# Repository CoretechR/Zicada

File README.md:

# Zicada - DIY Zigbee Multisensor

## Overview

Zicada is a DIY Zigbee sensor based on Nordic’s nRF52840 SoC. It combines a temperature and humidity sensor with a hall effect switch, making it suitable for both climate and door/window monitoring. Zicada is optimized for ultra-low power consumption, running at just 6µW in standby. This allows it to operate on a rechargeable AAA battery for 2 years or longer. It is fully compatible with Home Assistant (ZHA) and Zigbee2MQTT.

<div align="center">
  
</div>

### Features
* Temperature, humidity and contact sensing
* Zigbee 3.0 end device
* Compatible with Home Assistant (ZHA) and Zigbee2MQTT
* Ultra-low power consumption (6µW in Standby)
* 2+ years of battery life
* Supports AAA cells from 0.9V to 1.5V
* Small sized (62 x 15 mm) and fully 3D-printed case

### Setup Instructions

Follow these instructions to download and install the nRF Connect SDK version 2.6.0:
https://docs.nordicsemi.com/bundle/ncs-2.6.3/page/nrf/installation/install_ncs.html
Copy Zicada firmware folder into the directory ncs/projects.

When using the contact sensor with Zigbee2MQTT, copy the file "zicada_converter.js" to the directory data/external_converters/ of you Z2M install.

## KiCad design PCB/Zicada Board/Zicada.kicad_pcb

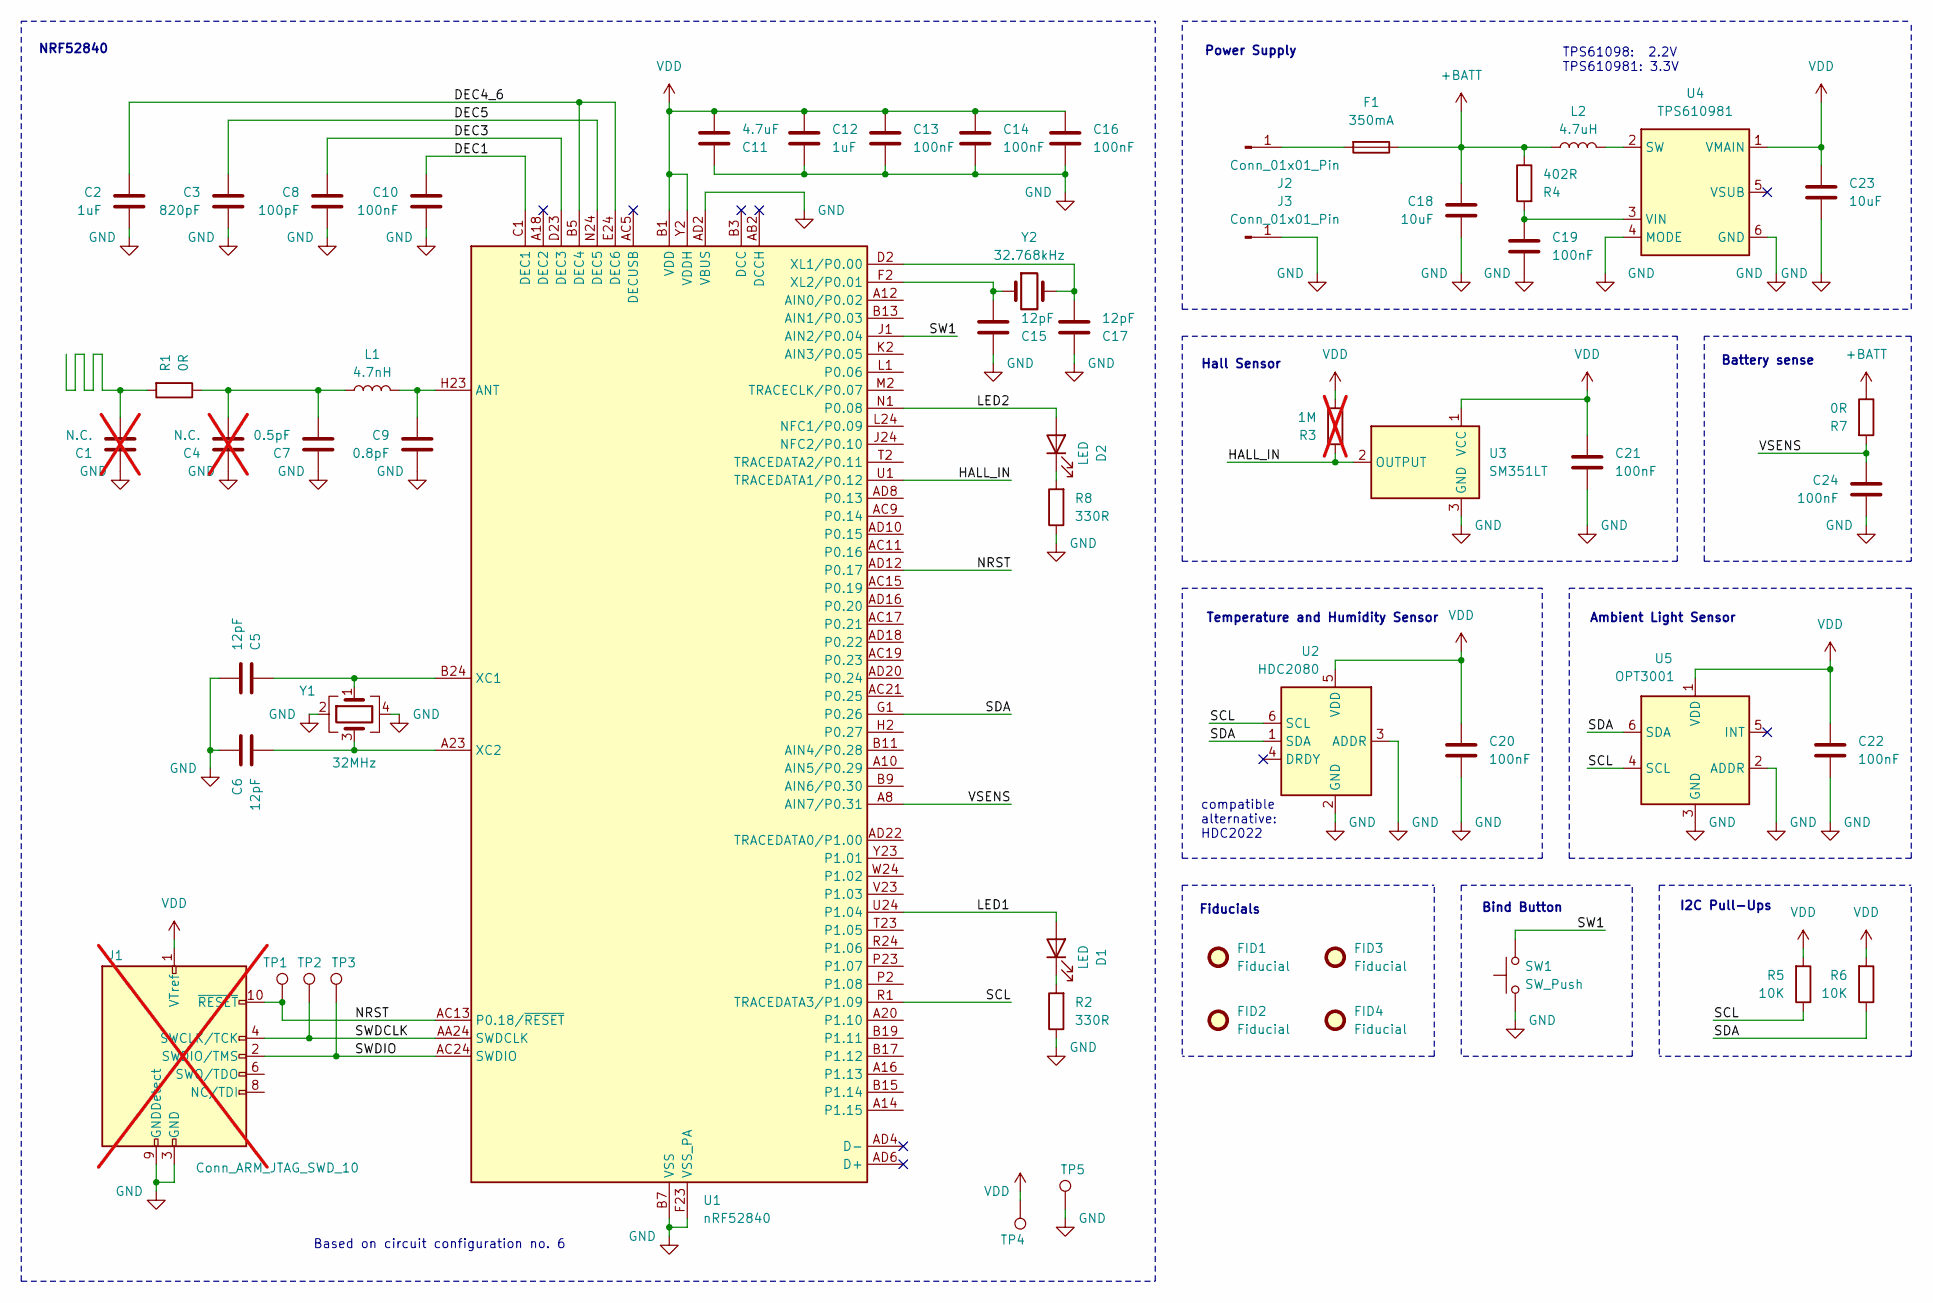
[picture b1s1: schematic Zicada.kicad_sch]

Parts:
C1, C4: N.C.; C_0603_1608Metric; not fitted
C2, C12: 1uF; C_0603_1608Metric; LCSC C15849
C3: 820pF; C_0603_1608Metric; LCSC C107057
C5, C6, C15, C17: 12pF; C_0603_1608Metric; LCSC C107034
C7: 0.5pF; C_0603_1608Metric; LCSC C5137584
C8: 100pF; C_0603_1608Metric; LCSC C14858
C9: 0.8pF; C_0603_1608Metric; LCSC C519369
C10, C13, C14, C16, C19, C20, C21, C22, C24: 100nF; C_0603_1608Metric; LCSC C1591
C11: 4.7uF; C_0603_1608Metric; LCSC C1705
C18, C23: 10uF; C_0603_1608Metric; LCSC C19702
D1, D2: LED; LED_0603_1608Metric; LCSC C5875723
F1: 350mA; Fuse_0805_2012Metric; LCSC C207021
FID1, FID2, FID3, FID4: Fiducial; Fiducial_1mm_Mask2mm
J1: Conn_ARM_JTAG_SWD_10; PinHeader_2x05_P1.27mm_Vertical_SMD; not fitted
J2, J3: Conn_01x01_Pin; MYOUNG MY-AAA-07; LCSC C6937109
L1: 4.7nH; L_0603_1608Metric; LCSC C1030
L2: 4.7uH; L_1008_2520Metric; LCSC C280597
R1, R7: 0R; R_0603_1608Metric; LCSC C116699
R2, R8: 330R; R_0603_1608Metric; LCSC C105881
R3: 1M; R_0603_1608Metric; LCSC C105578; not fitted
R4: 402R; R_0603_1608Metric; LCSC C227889
R5, R6: 10K; R_0603_1608Metric; LCSC C98220
SW1: SW_Push; SW_SPST_B3U-1000P-B; LCSC C231329
TP1, TP2, TP3, TP4, TP5: TestPoint; TestPoint_Pad_D1.5mm
U1: nRF52840; Nordic_AQFN-73-1EP_7x7mm_P0.5mm; LCSC C190794
U2: HDC2080; Texas_PWSON-N6; LCSC C918141
U3: SM351LT; SOT-23; LCSC C80830
U4: TPS610981; WSON-6_1.5x1.5mm_P0.5mm; LCSC C470966
U5: OPT3001; USON-6-1EP_2x2mm_P0.65mm_EP0.65x1.35mm; LCSC C90462
Y1: 32MHz; Crystal_SMD_Abracon_ABM8G-4Pin_3.2x2.5mm; LCSC C5552502
Y2: 32.768kHz; Crystal_SMD_MicroCrystal_CC7V-T1A-2Pin_3.2x1.5mm; LCSC C32346

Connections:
+BATT: C18.1, F1.1, L2.1, R4.1, R7.1
/DEC1: C10.1, U1.C1 (DEC1)
/DEC3: C8.1, U1.D23 (DEC3)
/DEC4_6: C2.1, U1.B5 (DEC4), U1.E24 (DEC6)
/DEC5: C3.1, U1.N24 (DEC5)
/HALL_IN: R3.2, U1.U1 (TRACEDATA1/P0.12), U3.2 (OUTPUT)
/LED1: D1.2 (A), U1.U24 (P1.04)
/LED2: D2.2 (A), U1.N1 (P0.08)
/NRST: J1.10 (~RESET), TP1.1, U1.AC13 (P0.18/~RESET), U1.AD12 (P0.17)
/SCL: R5.1, U1.R1 (TRACEDATA3/P1.09), U2.6 (SCL), U5.4 (SCL)
/SDA: R6.1, U1.G1 (P0.26), U2.1 (SDA), U5.6 (SDA)
/SW1: SW1.2, U1.J1 (AIN2/P0.04)
/SWDCLK: J1.4 (SWCLK/TCK), TP2.1, U1.AA24 (SWDCLK)
/SWDIO: J1.2 (SWDIO/TMS), TP3.1, U1.AC24 (SWDIO)
/VSENS: C24.1, R7.2, U1.A8 (AIN7/P0.31)
GND: C1.1, C2.2, C3.2, C4.1, C5.2, C6.1, C7.1, C8.2, C9.2, C10.2, C11.1, C12.2, C13.2, C14.2, C15.1, C16.2, C17.1, C18.2, C19.2, C20.2, C21.2, C22.2, C23.2, C24.2, J1.3 (GND), J1.5 (GND), J1.9 (GNDDetect), J3.1, R2.1, R8.1, SW1.1, TP5.1, U1.AD2 (VBUS), U1.B7 (VSS), U1.EP (VSS), U1.F23 (VSS_PA), U2.2 (GND), U2.3 (ADDR), U3.3 (GND), U4.4 (MODE), U4.6 (GND), U5.2 (ADDR), U5.3 (GND), Y1.2, Y1.4
unnamed: C1.2, R1.2
unnamed: C4.2, C7.2, L1.1, R1.1
unnamed: D1.1 (K), R2.2
unnamed: D2.1 (K), R8.2
unnamed: F1.2, J2.1
unnamed: C9.1, L1.2, U1.H23 (ANT)
unnamed: C5.1, U1.B24 (XC1), Y1.1
unnamed: C6.2, U1.A23 (XC2), Y1.3
unnamed: C17.2, U1.D2 (XL1/P0.00), Y2.2
unnamed: C15.2, U1.F2 (XL2/P0.01), Y2.1
unnamed: L2.2, U4.2 (SW)
unnamed: C19.1, R4.2, U4.3 (VIN)
VDD: C11.2, C12.1, C13.1, C14.1, C16.1, C20.1, C21.1, C22.1, C23.1, J1.1 (VTref), R3.1, R5.2, R6.2, TP4.1, U1.A22 (VDD), U1.AD14 (VDD), U1.AD23 (VDD), U1.B1 (VDD), U1.W1 (VDD), U1.Y2 (VDDH), U2.5 (VDD), U3.1 (VCC), U4.1 (VMAIN), U5.1 (VDD)

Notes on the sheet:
NRF52840
Ambient Light Sensor
Temperature and Humidity Sensor
Based on circuit configuration no. 6
compatible alternative: HDC2022
Bind Button
Power Supply
TPS61098: 2.2V TPS610981: 3.3V
Fiducials
Battery sense
I2C Pull-Ups
Hall Sensor

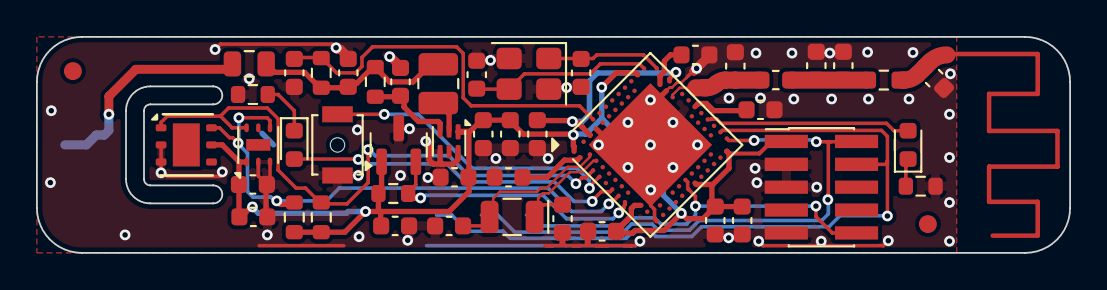
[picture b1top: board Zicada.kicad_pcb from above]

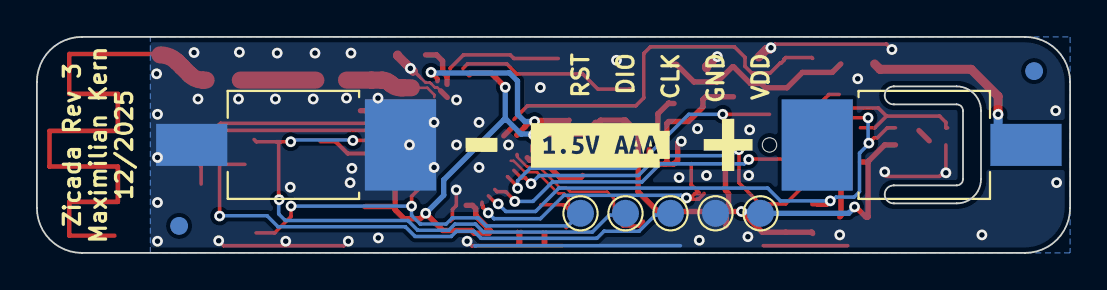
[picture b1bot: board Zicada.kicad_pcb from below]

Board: 2 copper layers, 57.4 x 12.0 mm, 60 parts (12 on the bottom side), 29 nets.

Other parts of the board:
kibuzzard-6898F1CE: G***; kibuzzard-6898F1CE
kibuzzard-6898F6DD: G***; kibuzzard-6898F6DD
kibuzzard-6898F105: G***; kibuzzard-6898F105

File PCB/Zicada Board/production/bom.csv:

Designator,Footprint,Quantity,Value,LCSC Part #
"C10, C13, C14, C16, C19, C20, C21, C22, C24",0603,9,100nF,C1591
C11,0603,1,4.7uF,C1705
"C12, C2",0603,2,1uF,C15849
"C15, C17, C5, C6",0603,4,12pF,C107034
"C18, C23",0603,2,10uF,C19702
C3,0603,1,820pF,C107057
C7,0603,1,0.5pF,C5137584
C8,0603,1,100pF,C14858
C9,0603,1,0.8pF,C519369
"D1, D2",0603,2,LED,C5875723
F1,0805,1,350mA,C207021
"J2, J3",MYOUNG MY-AAA-07,2,Conn_01x01_Pin,C6937109
L1,0603,1,4.7nH,C1030
L2,1008,1,4.7uH,C280597
"R1, R7",0603,2,0R,C116699
"R2, R8",0603,2,330R,C105881
R4,0603,1,402R,C227889
"R5, R6",0603,2,10K,C98220
SW1,SW_SPST_B3U-1000P-B,1,SW_Push,C231329
U1,Nordic_AQFN-73-1EP_7x7mm_P0.5mm,1,nRF52840,C190794
U2,Texas_PWSON-N6,1,HDC2080,C918141
U3,SOT-23,1,SM351LT,C80830
U4,WSON-6_1.5x1.5mm_P0.5mm,1,TPS610981,C470966
U5,USON-6-1EP_2x2mm_P0.65mm_EP0.65x1.35mm,1,OPT3001,C90462
Y1,Crystal_SMD_Abracon_ABM8G-4Pin_3.2x2.5mm,1,32MHz,C5552502
Y2,Crystal_SMD_MicroCrystal_CC7V-T1A-2Pin_3.2x1.5mm,1,32.768kHz,C32346

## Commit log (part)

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2025-11-16 Fix image filename case in README.md
2025-12-29 Added OPT3001 sensor
2025-12-31 generated fabrication files
2026-02-08 V2 CAD files added
    These optional files include holes for improved airflow in the from case as well as a larger button needed for light sensing
2026-02-08 Added OPT3001 to the firmware and converter
    - OPT3001 now included in the board config
    - illuminance clutser added to the zigbee config
    - z2m converter file updated
2026-03-29 Fixed attribute reporting issue
    This should fix an issue where attributes are not properly configured with Zigbee2MQTT.
2026-04-04 Fixed ZB_ZICADA_REPORT_ATTR_COUNT
    The wrong attribute count was causing random boot loops.
